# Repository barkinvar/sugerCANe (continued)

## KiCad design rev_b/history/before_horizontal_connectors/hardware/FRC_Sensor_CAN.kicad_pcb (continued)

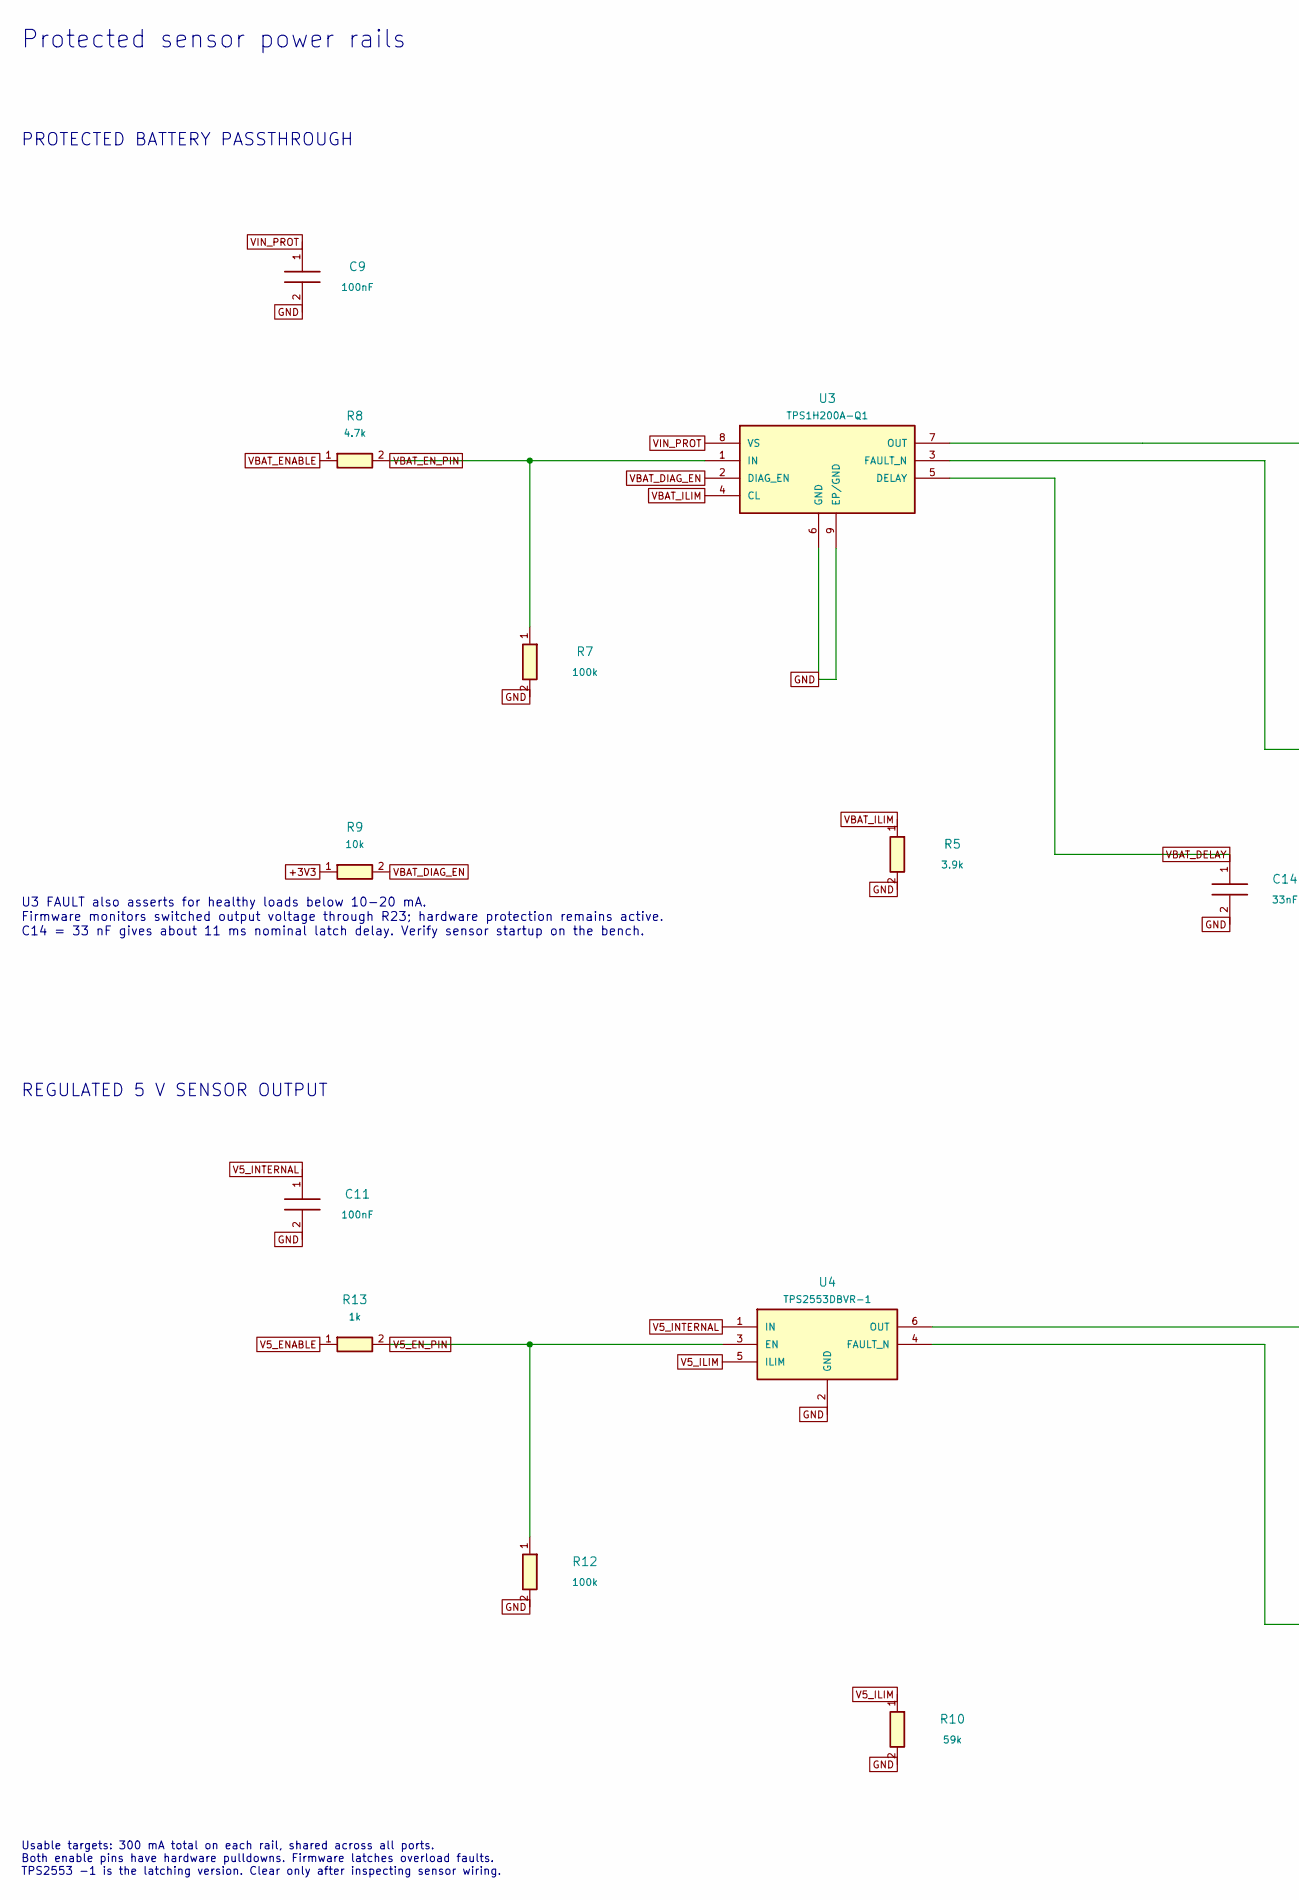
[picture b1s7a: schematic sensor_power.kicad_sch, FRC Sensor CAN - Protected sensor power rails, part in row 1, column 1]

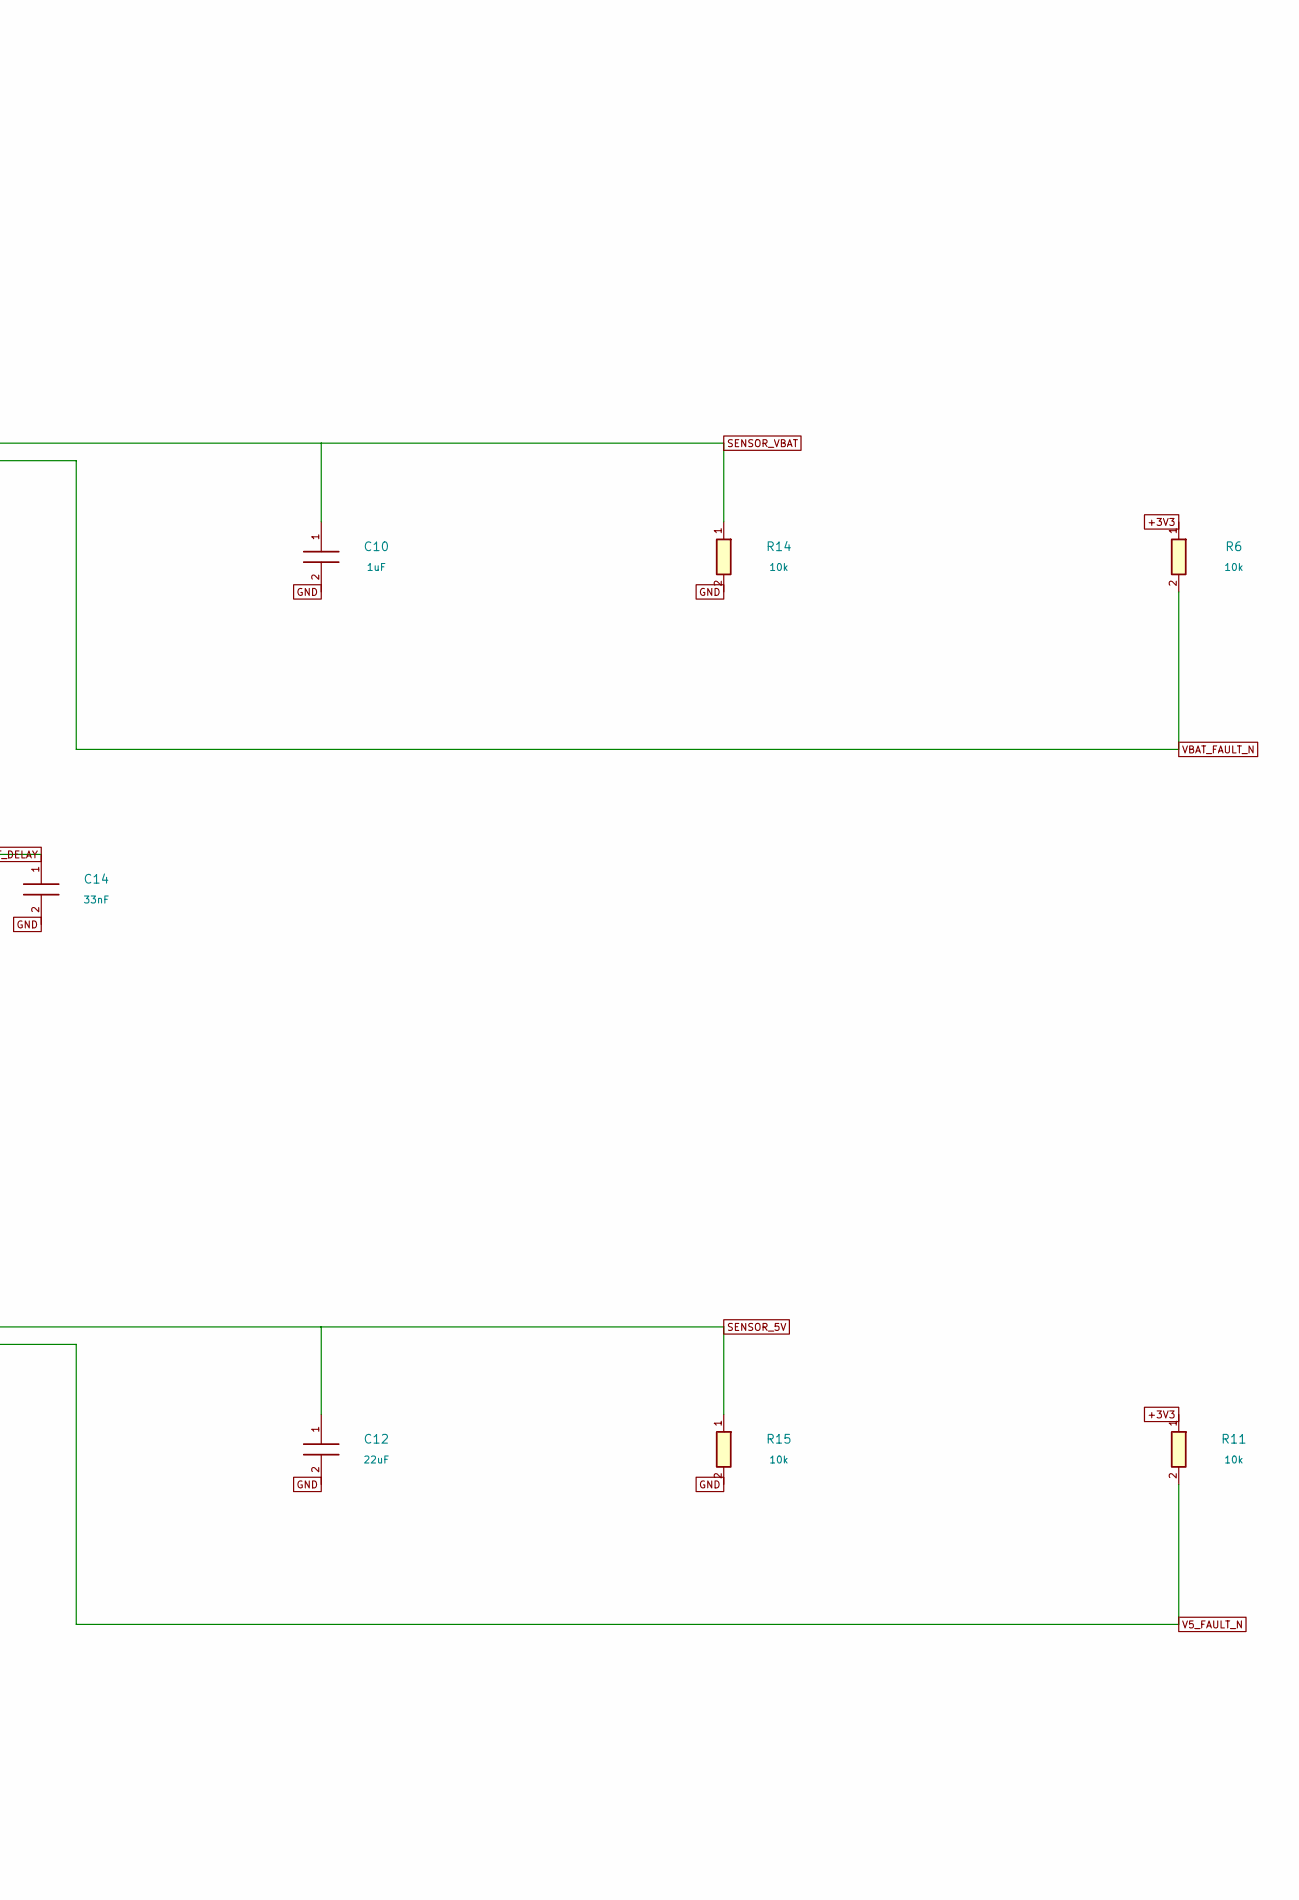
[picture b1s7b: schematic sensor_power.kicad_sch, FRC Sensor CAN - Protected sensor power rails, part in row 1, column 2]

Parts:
C9, C11: 100nF; C_0805_2012Metric; MPN CC0805KRX7R9BB104
C10: 1uF; C_0805_2012Metric; MPN CC0805KKX7R9BB105
C12: 22uF; C_1206_3216Metric; MPN CL31A226KAHNNNE
C14: 33nF; C_0805_2012Metric; MPN CC0805KRX7R9BB333
R5: 3.9k; R_0805_2012Metric; MPN RC0805FR-073K9L
R6, R9, R11, R14, R15: 10k; R_0805_2012Metric; MPN RC0805FR-0710KL
R7, R12: 100k; R_0805_2012Metric; MPN RC0805FR-07100KL
R8: 4.7k; R_0805_2012Metric; MPN RC0805FR-074K7L
R10: 59k; R_0805_2012Metric; MPN RC0805FR-0759KL
R13: 1k; R_0805_2012Metric; MPN RC0805FR-071KL
U3: TPS1H200A-Q1; TI_DGN0008K_HVSSOP8_EP; MPN TPS1H200AQDGNRQ1
U4: TPS2553DBVR-1; SOT-23-6; MPN TPS2553DBVR-1

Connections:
+3V3: R6.1, R9.1, R11.1; also elsewhere on the board
GND: C9.2, C10.2, C11.2, C12.2, C14.2, R5.2, R7.2, R10.2, R12.2, R14.2, R15.2, U3.6 (GND), U3.9 (EP/GND), U4.2 (GND); also elsewhere on the board
SENSOR_5V: C12.1, R15.1, U4.6 (OUT); also elsewhere on the board
SENSOR_VBAT: C10.1, R14.1, U3.7 (OUT); also elsewhere on the board
V5_ENABLE: R13.1; also elsewhere on the board
V5_EN_PIN: R12.1, R13.2, U4.3 (EN)
V5_FAULT_N: R11.2, U4.4 (FAULT_N); also elsewhere on the board
V5_ILIM: R10.1, U4.5 (ILIM)
V5_INTERNAL: C11.1, U4.1 (IN); also elsewhere on the board
VBAT_DELAY: C14.1, U3.5 (DELAY)
VBAT_DIAG_EN: R9.2, U3.2 (DIAG_EN)
VBAT_ENABLE: R8.1; also elsewhere on the board
VBAT_EN_PIN: R7.1, R8.2, U3.1 (IN)
VBAT_FAULT_N: R6.2, U3.3 (FAULT_N); also elsewhere on the board
VBAT_ILIM: R5.1, U3.4 (CL)
VIN_PROT: C9.1, U3.8 (VS); also elsewhere on the board

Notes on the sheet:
Protected sensor power rails
PROTECTED BATTERY PASSTHROUGH
U3 FAULT also asserts for healthy loads below 10-20 mA. Firmware monitors switched output voltage through R23; hardware protection remains active. C14 = 33 nF gives about 11 ms nominal latch delay. Verify sensor startup on the bench.
REGULATED 5 V SENSOR OUTPUT
Usable targets: 300 mA total on each rail, shared across all ports. Both enable pins have hardware pulldowns. Firmware latches overload faults. TPS2553 -1 is the latching version. Clear only after inspecting sensor wiring.

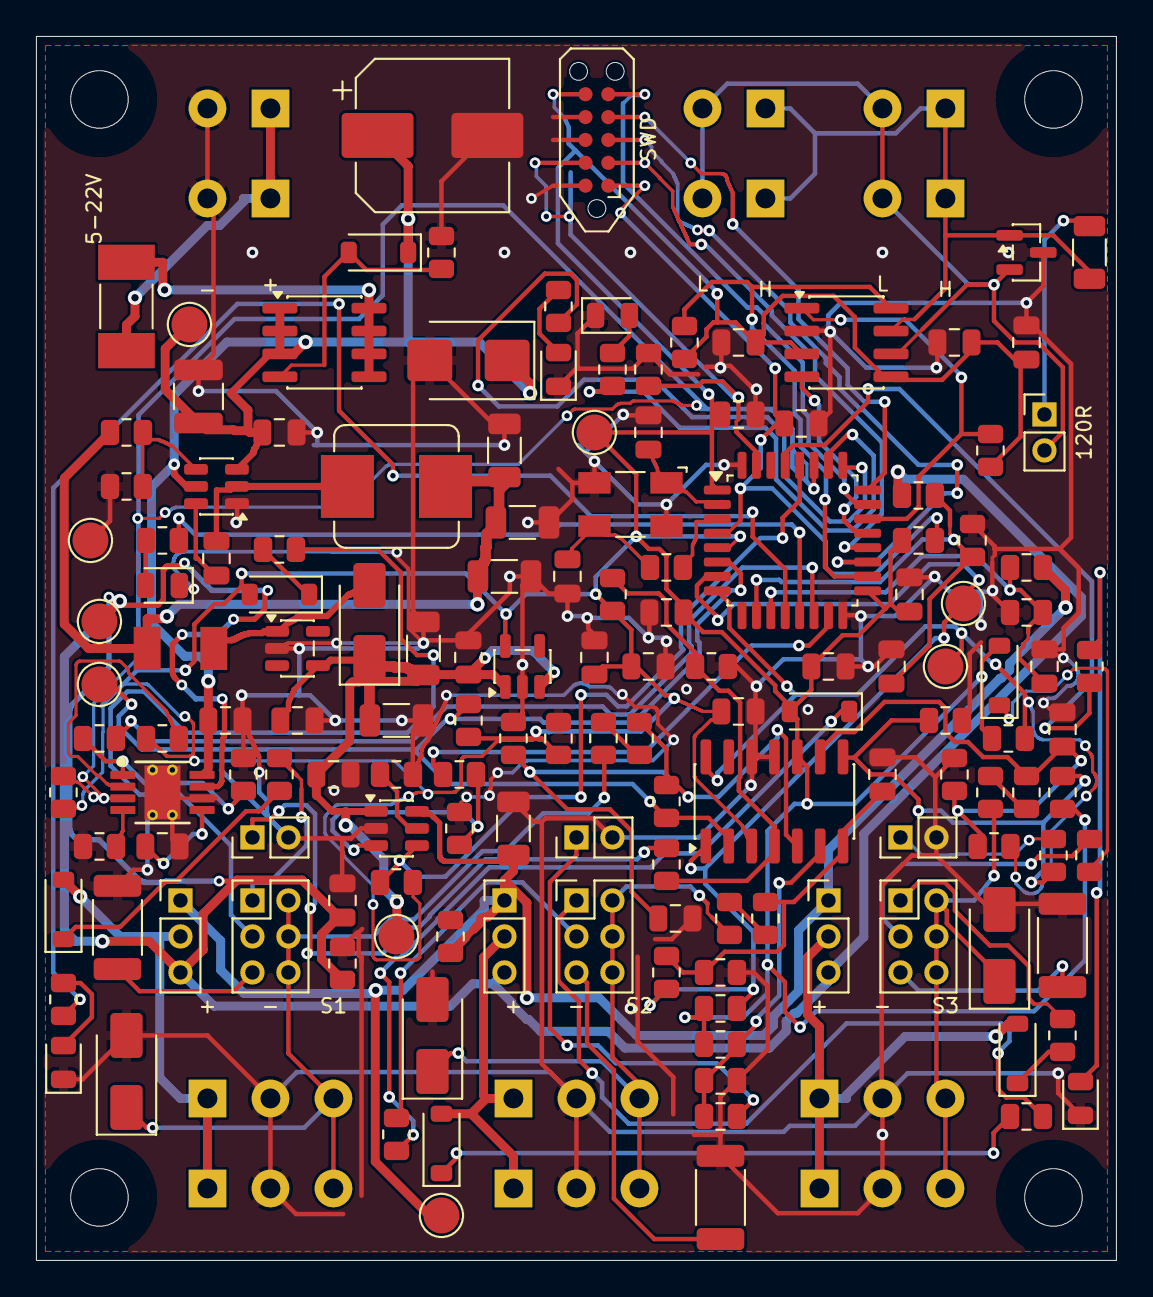
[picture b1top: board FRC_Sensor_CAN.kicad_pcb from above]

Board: 2 copper layers, 60.0 x 68.0 mm, 158 parts (0 on the bottom side), 87 nets.

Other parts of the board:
C15, C16: 22uF; C_1206_3216Metric
C17: 100nF; C_0805_2012Metric
D4: SS14; D_SMA
H1, H2, H3, H4: M3 NPTH
L2: 4.7uH; Bourns_SRP4020TA
U8: TPS613222A; SOT-23-5

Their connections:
BOOST_SW: D4.2, L2.2, U8.1
GND: C15.2, C16.2, C17.2, U8.2; also elsewhere on the board
V4P2: L2.1; also elsewhere on the board
V5_INTERNAL: C15.1, C16.1, C17.1, D4.1, U8.4; also elsewhere on the board

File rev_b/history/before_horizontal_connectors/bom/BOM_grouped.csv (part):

MPN,Manufacturer,DigiKey_SKU,Quantity,References,Value,Footprint,Voltage,Tolerance,Power_W,Dielectric,Component_notes,Unit_USD_qty1,Extended_USD_qty1,Observed_stock,Checked_date,DigiKey_URL,Notes
045101.5MRL,Littelfuse,F2579CT-ND,1,F1,1.5A FAST,FRC_Sensor_CAN:Fuse_Littelfuse-NANO2-451_453,,,,,Secondary protection; feed only from fused robot distribution.,2.47,2.47,7870,2026-09-07,https://www.digikey.com/en/products/detail/littelfuse-inc/04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,1.5A fast NANO2 fuse; upstream fused distribution still required.
1885650000,Weidmuller,281-2809-ND,3,"J1, J2, J3",2P PUSH 3.5mm,FRC_Sensor_CAN:Weidmuller_LSF_135_2P,,,,,"Weidmuller push-in actuator, 8 mm strip; two solder pins per electrical pole.",1.5,4.5,698,2026-09-08,https://www.digikey.com/en/products/detail/weidm%C3%BCller/1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,US listing/filter price; regional stock observations vary. See sourcing notes.
1885660000,Weidmuller,281-2810-ND,3,"J4, J5, J6",3P PUSH 3.5mm,FRC_Sensor_CAN:Weidmuller_LSF_135_3P,,,,,"Weidmuller push-in actuator, 8 mm strip; two solder pins per electrical pole.",2.1,6.3,410,2026-09-08,https://www.digikey.com/en/products/detail/weidm%C3%BCller/1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,"3.50 mm pitch, 3.5 mm pins, 135-degree push-in. Manufacturer current drawing controls dimensions."
ABM3B-8.000MHZ-B2-T,Abracon,535-9720-1-ND,1,Y1,8MHz 18pF,FRC_Sensor_CAN:Abracon_ABM3B_5.0x3.2mm,,,,,Abracon recommended land pattern: 1.8x1.2mm pads on 4.0x2.4mm centers; pads 2/4 ground.,0.76,0.76,70541,2026-09-07,https://www.digikey.com/en/products/detail/abracon-llc/ABM3B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,"18pF load, ESR<=200ohm, 20ppm initial/50ppm stability, -20..70C."
AO4485,Alpha & Omega Semiconductor,785-1551-1-ND,1,Q1,AO4485,FRC_Sensor_CAN:SOIC-8_3.9x4.9mm_P1.27mm,,,,,"Reverse-polarity PMOS: drain toward input, source toward load. Not a reverse-current blocker when on.",1.51,1.51,64905,2026-09-07,https://www.digikey.com/en/products/detail/alpha-omega-semic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,"40V P-channel,SOIC8,20mohm max at-4.5V gate. Datasheet pin mapping checked."
AP2112K-3.3TRG1,Diodes Incorporated,AP2112K-3.3TRG1DICT-ND,1,U2,AP2112K-3.3,FRC_Sensor_CAN:SOT-23-5,,,,,,0.28,0.28,159040,2026-09-07,https://www.digikey.com/en/products/detail/diodes-incorporat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,
BAT46W-E3-18,Vishay,BAT46W-E3-18GICT-ND,6,"D102, D103, D202, D203, D302, D303",BAT46W,FRC_Sensor_CAN:D_SOD-123,,,,,,0.52,3.12,19931,2026-09-07,https://www.digikey.com/en/products/detail/vishay-general-se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,"100V reverse blocking, SOD123. Catalog showed$0.49-$0.52 by packaging; conservative price used. Do not substitute30V BAT54."
C0805C300J5GACTU,KEMET,399-C0805C300J5GACTUCT-ND,2,"C25, C26",30pF,FRC_Sensor_CAN:C_0805_2012Metric,50V,5%,,C0G,,0.33,0.66,9211,2026-09-07,https://www.digikey.com/en/products/detail/kemet/C0805C300J5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,"30pF,50V,C0G,5%,0805."
CC0805JRNPO9BN102,YAGEO,311-1122-1-ND,3,"C101, C201, C301",1nF,FRC_Sensor_CAN:C_0805_2012Metric,50V,5%,,C0G,,0.15,0.45,105431,2026-09-07,https://www.digikey.com/en/products/detail/yageo/CC0805JRNPO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,"1nF,50V,C0G,5%,0805."
CC0805KKX7R9BB105,YAGEO,311-1886-1-ND,4,"C7, C10, C23, C42",1uF,FRC_Sensor_CAN:C_0805_2012Metric,50V,10%,,X7R,,0.32,1.28,112870,2026-09-07,https://www.digikey.com/en/products/detail/yageo/CC0805KKX7R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,"1uF,50V,X7R,10%,0805. Lower-cost stocked selection."
CC0805KRX7R9BB103,YAGEO,311-1136-1-ND,2,"C28, C29",10nF,FRC_Sensor_CAN:C_0805_2012Metric,50V,10%,,X7R,,0.11,0.22,360198,2026-09-07,https://www.digikey.com/en/products/detail/yageo/CC0805KRX7R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,"10nF,50V,X7R,0805; stock from DigiKey substitute table."
CC0805KRX7R9BB104,YAGEO,311-1140-1-ND,12,"C3, C6, C9, C11, C20, C21, C22, C27, C40, C41, C50, C17",100nF,FRC_Sensor_CAN:C_0805_2012Metric,50V,10%,,X7R,,0.11,1.32,1921549,2026-09-07,https://www.digikey.com/en/products/detail/yageo/CC0805KRX7R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,"100nF,50V,X7R,0805; stock from DigiKey substitute table."
CC0805KRX7R9BB333,YAGEO,311-1374-1-ND,1,C14,33nF,FRC_Sensor_CAN:C_0805_2012Metric,50V,10%,,X7R,Hardware latch-off after ~11ms in current limit; allows sensor inrush; no automatic retry.,0.14,0.14,24641,2026-09-07,https://www.digikey.com/en/products/detail/yageo/CC0805KRX7R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,"33nF,50V,X7R,10%,0805; battery switch latch timing. Direct US product listing checked2026-09-07."
CL31A226KAHNNNE,Samsung Electro-Mechanics,1276-3047-1-ND,6,"C4, C5, C13, C12, C15, C16",22uF,FRC_Sensor_CAN:C_1206_3216Metric,25V,10%,,X5R,,0.48,2.88,426249,2026-09-07,https://www.digikey.com/en/products/detail/samsung-electro-m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,22uF25VX5R1206. Manufacturer typical capacitance change is about-39% near5.18V; three parallel capacitors used on buck output.
CL32B106KBJNNWE,Samsung Electro-Mechanics,1276-3388-1-ND,1,C2,10uF,FRC_Sensor_CAN:C_1210_3225Metric,50V,10%,,X7R,,0.62,0.62,149003,2026-09-07,https://www.digikey.com/en/products/detail/samsung-electro-m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,"10uF,50V,X7R,1210; DigiKey US Spanish-language catalog observation."
EEE-FK1H470P,Panasonic,PCE3815CT-ND,1,C1,47uF,FRC_Sensor_CAN:CP_Elec_8x6.5,50V,20%,,,,0.93,0.93,10108,2026-09-08,https://www.digikey.com/en/products/detail/panasonic-industr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,"50 V, 47 uF, 8 mm diameter, 6.5 mm maximum seated height."
ERJ-6ENF1782V,Panasonic Industry,P17.8KCCT-ND,4,"R2, R107, R207, R307",17.8k,FRC_Sensor_CAN:R_0805_2012Metric,,1%,0.125,,,0.12,0.48,33381,2026-09-07,https://www.digikey.com/en/products/detail/panasonic-industr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,
ESD2CAN24DBZRQ1,Texas Instruments,296-ESD2CAN24DBZRQ1CT-ND,1,D20,ESD2CAN24-Q1,FRC_Sensor_CAN:SOT-23,,,,,,0.87,0.87,255809,2026-09-07,https://www.digikey.com/en/products/detail/texas-instruments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,
LM339LVDR,Texas Instruments,296-LM339LVDRCT-ND,1,U7,LM339LV,FRC_Sensor_CAN:SOIC-14_3.9x8.7mm_P1.27mm,,,,,Rail-to-rail failsafe comparator on regulated 3V3. 0-30V signal is divided before this pin; NOT a 30V supply IC. Same SO14 pin assignment as LM2901B.,0.42,0.42,1085,2026-09-08,https://www.digikey.com/en/products/detail/texas-instruments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,"1.65-5.5 V supply, rail-to-rail failsafe inputs. Supplied from 3V3; not interchangeable with battery-supplied Rev A without changing supply."
LMR51420XDDCR,Texas Instruments,296-LMR51420XDDCRCT-ND,1,U1,LMR51420XDDCR,FRC_Sensor_CAN:TSOT-23-6,,,,,,1.32,1.32,14239,2026-09-07,https://www.digikey.com/en/products/detail/texas-instruments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,
LTST-C170KGKT,Lite-On,160-1414-1-ND,4,"D10, D12, D13, D14",GREEN,FRC_Sensor_CAN:LED_0805_2012Metric,,,,,,0.19,0.76,498450,2026-09-07,https://www.digikey.com/en/products/detail/lite-on-inc/LTST-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,"Green0805,typical Vf2V. Board current approximately1.3mA."
LTST-C170KRKT,Lite-On,160-1415-1-ND,1,D11,RED,FRC_Sensor_CAN:LED_0805_2012Metric,,,,,,0.18,0.18,489805,2026-09-07,https://www.digikey.com/en/products/detail/lite-on-inc/LTST-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,"Red0805,typical Vf2V. Board current approximately1.3mA."
M22-1900005,Harwin,952-1305-ND,10,10 configuration shunts,2 mm shunt,Off-board assembly accessory,,,,,,0.35,3.5,31908,2026-09-08,https://www.digikey.com/en/products/detail/harwin-inc/M22-19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,2 mm shunt; ten supplied allow all modes plus optional termination.
M22-2010205,Harwin,952-2273-ND,4,"JP2, JP102, JP202, JP302",SELECT,FRC_Sensor_CAN:PinHeader_1x02_P2.00mm_Vertical,,,,,Optional 120-ohm termination: shipped OPEN.,0.16,0.64,7644,2026-09-08,https://www.digikey.com/en/products/detail/harwin-inc/M22-20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,"2 mm pitch, 1 A contact."
M22-2010305,Harwin,952-2274-ND,3,"JP101, JP201, JP301",SELECT,FRC_Sensor_CAN:PinHeader_1x03_P2.00mm_Vertical,,,,,"Fit ONE shunt: 1-2=5V, 2-3=VBAT. Never bridge all pins.",0.22,0.66,35632,2026-09-08,https://www.digikey.com/en/products/detail/harwin-inc/M22-20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,"2 mm pitch, 1 A contact."
M22-2020305,Harwin,952-2133-ND,3,"JP103, JP203, JP303",SELECT,FRC_Sensor_CAN:PinHeader_2x03_P2.00mm_Vertical,,,,,"ONE horizontal shunt only:1-2=port pullup,3-4=3V3 pullup,5-6=pulldown. Open=driven input.",0.41,1.23,838,2026-09-08,https://www.digikey.com/en/products/detail/harwin-inc/M22-20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,"2 x 3, 2 mm pitch in both directions."
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
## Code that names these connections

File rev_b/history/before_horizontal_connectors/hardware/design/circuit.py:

"""Compact three-channel revision B; explicit changes to the frozen A circuit."""
from pathlib import Path
from copy import deepcopy
import json
from circuit_rev_a import PARTS as A
ROOT=Path(__file__).resolve().parents[2]
PARTS=deepcopy(A)
for ref in list(PARTS):
    if PARTS[ref]['sheet']=='input4' or ref in ['D15','R35','JP1']:
        del PARTS[ref]
PARTS['U5']['pins']['9']=None
PARTS['U5']['pins']['30']=None
PARTS['U7']['pins'].update({'13':None,'11':'GND','10':'+3V3','3':'+3V3'})
PARTS['U7'].update(value='LM339LV',mpn='LM339LVDR',note='Rail-to-rail failsafe comparator on regulated 3V3. 0-30V signal is divided before this pin; NOT a 30V supply IC. Same SO14 pin assignment as LM2901B.')
PARTS['C50']['pins']['1']='+3V3'
PARTS['D2'].update(value='SMBJ22A',mpn='SMBJ22A-E3/52',note='22 V continuous standoff; 35.5 V specified pulse clamp. Bench-check overshoot. Not sustained overvoltage regulation.')
PARTS['C1'].update(voltage='50V',mpn='EEE-FK1H470P',footprint='FRC_Sensor_CAN:CP_Elec_8x6.5',source_footprint='Capacitor_SMD:CP_Elec_8x6.5')
PARTS['R3']['note']='Gate pull-down; maximum 1 mA nominal zener current at 22 V input.'
PARTS['R14']['note']='Switched battery output bleed; 2.2 mA at 22 V.'
PARTS['R1'].update(value='100k',mpn='RC0805FR-07100KL',tolerance='1%')
PARTS['R2'].update(value='17.8k',mpn='ERJ-6ENF1782V',tolerance='1%')
for ref in ['L1','C4','C5','C13','R1']:
    PARTS[ref]['pins']={k:('V4P2' if n=='V5_INTERNAL' else n) for k,n in PARTS[ref]['pins'].items()}
for ref in ['J1','J2','J3','J4','J5','J6']:
    c=PARTS[ref];n=len(c['pins'])
    c.update(value=f'{n}P PUSH 3.5mm',mpn='1885650000' if n==2 else '1885660000',
        footprint=f'FRC_Sensor_CAN:Weidmuller_LSF_135_{n}P',source_footprint=f'FRC_Sensor_CAN:Weidmuller_LSF_135_{n}P',
        note='Weidmuller push-in actuator, 8 mm strip; two solder pins per electrical pole.')
for ref,c in PARTS.items():
    if ref.startswith('JP'):
        n=len(c['pins']);cols=2 if n==6 else 1;rows=n//cols
        name=f'PinHeader_{cols}x{rows:02d}_P2.00mm_Vertical'
        c.update(mpn={2:'M22-2010205',3:'M22-2010305',6:'M22-2020305'}[n],
            footprint='FRC_Sensor_CAN:'+name,source_footprint='Connector_PinHeader_2.00mm:'+name)
PARTS['J8'].update(value='POGO SERVICE',mpn='',exclude_bom=True,
    footprint='FRC_Sensor_CAN:Tag-Connect_TC2050-IDC-NL_2x05_P1.27mm_Vertical',source_footprint='Connector:Tag-Connect_TC2050-IDC-NL_2x05_P1.27mm_Vertical',
    note='Standard TC2050-IDC-NL mechanical footprint; CUSTOM electrical pinout. Cable pin6 VTref output only. Follow adapter wiring table.')
PARTS['J8']['pins']={'1':'NRST','2':'UART_RX','3':'UART_TX','4':'SWCLK','5':'SWDIO','6':'+3V3','7':'GND','8':'GND','9':'BOOT0','10':'GND'}
def add(ref,kind,value,pins,fp,mpn,note='',**kw):
    PARTS[ref]=dict(ref=ref,kind=kind,value=value,pins={str(k):v for k,v in pins.items()},sheet='boost',
        footprint='FRC_Sensor_CAN:'+fp.split(':')[1],source_footprint=fp,mpn=mpn,note=note,**kw)
add('U8','BOOST','TPS613222A',{1:'BOOST_SW',2:'GND',3:None,4:'V5_INTERNAL',5:None},
    'Package_TO_SOT_SMD:SOT-23-5','TPS613222ADBVR','Fixed 5 V boost; powered through L2 from 4.0 V buck. DBV pins checked against TI table.')
add('L2','L','4.7uH',{1:'V4P2',2:'BOOST_SW'},'FRC_Sensor_CAN:Bourns_SRP4020TA','SRP4020TA-4R7M',
    '2.6 A RMS / 3.5 A saturation, 105 milliohm max; supports converter current-limit excursions.')
add('D4','D','SS14',{1:'V5_INTERNAL',2:'BOOST_SW'},'Diode_SMD:D_SMA','SS14-E3/61T',
    'External Schottky rectifier shares boost current as recommended by TI for 500 mA designs.')
for ref in ['C15','C16']:
    add(ref,'C','22uF',{1:'V5_INTERNAL',2:'GND'},'Capacitor_SMD:C_1206_3216Metric','CL31A226KAHNNNE',
        'Boost output reservoir; check effective capacitance and converter loop on bench.',voltage='25V',dielectric='X5R',tolerance='10%')
add('C17','C','100nF',{1:'V5_INTERNAL',2:'GND'},'Capacitor_SMD:C_0805_2012Metric','CC0805KRX7R9BB104',voltage='50V',dielectric='X7R',tolerance='10%')
def export():
    p=ROOT/'hardware/design/circuit.json'
    p.write_text(json.dumps({'revision':'B','parts':PARTS},indent=2)+'\n')
    print(len(PARTS),'parts;',len({n for c in PARTS.values() for n in c['pins'].values() if n}),'named nets')
if __name__=='__main__': export()
